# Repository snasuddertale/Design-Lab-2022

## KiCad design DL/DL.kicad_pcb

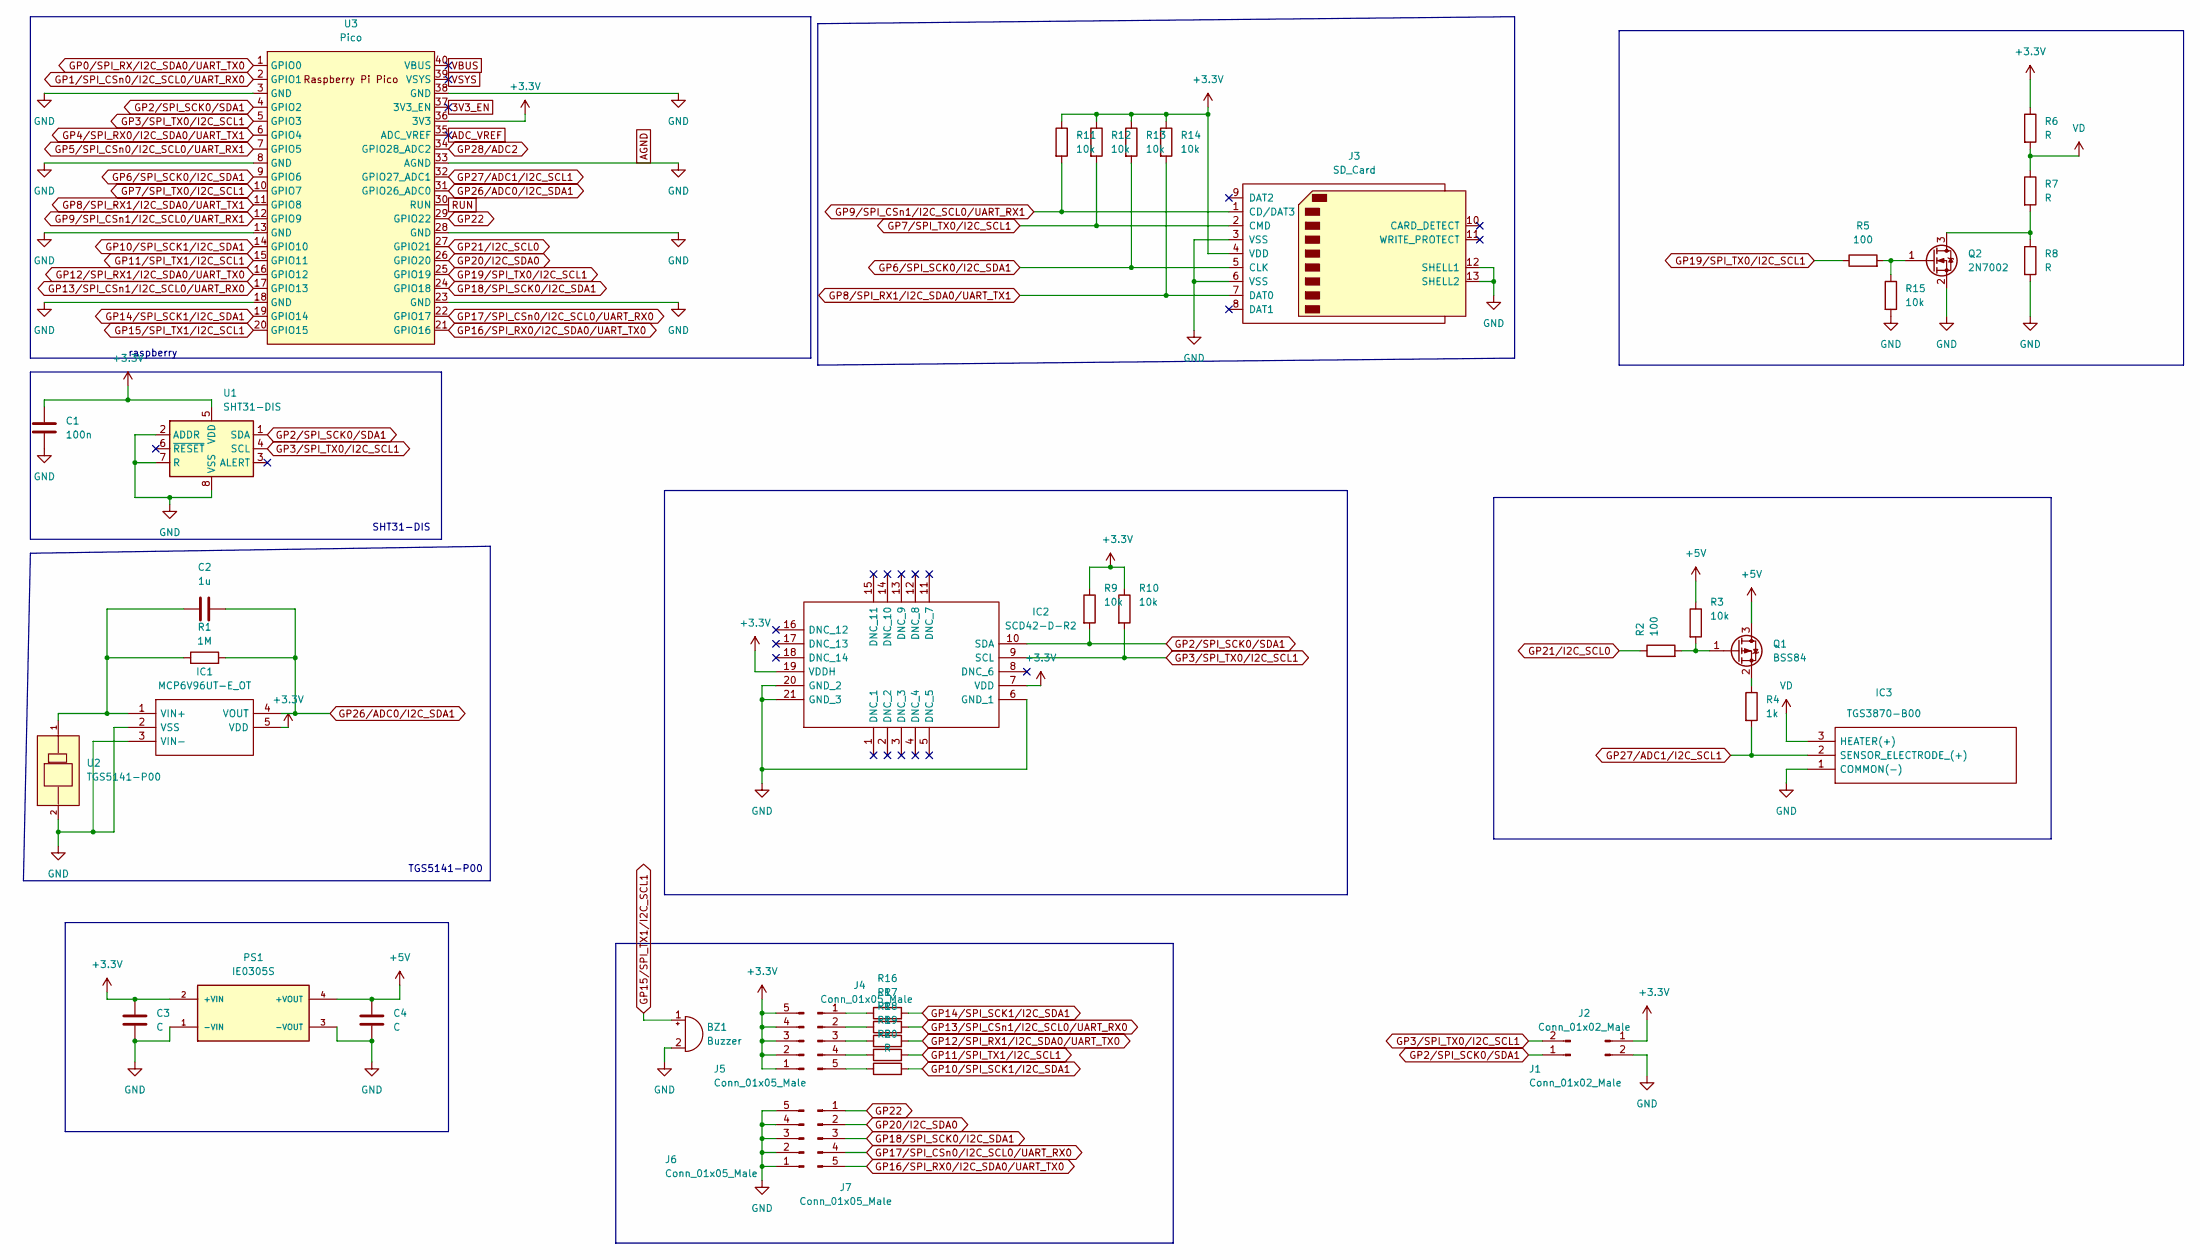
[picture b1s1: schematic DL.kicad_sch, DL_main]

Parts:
BZ1: Buzzer; Buzzer_12x9.5RM7.6
C1: 100n; C_0805_2012Metric_Pad1.18x1.45mm_HandSolder
C2: 1u; C_0805_2012Metric_Pad1.18x1.45mm_HandSolder
C3, C4: C; C_0805_2012Metric_Pad1.18x1.45mm_HandSolder
IC1: MCP6V96UT-E_OT; SOT95P280X145-5N; Mouser Part Number 579-MCP6V96UT-E/OT
IC2: SCD42-D-R2; SCD42DR2; Manufacturer_Part_Number SCD42-D-R2; Mouser Part Number 403-SCD42-D-R2
IC3: TGS3870-B00; TGS3870B00; Manufacturer_Part_Number TGS3870-B00
J1, J2: Conn_01x02_Male; PinHeader_1x02_P2.54mm_Vertical
J3: SD_Card; SD_Kyocera_145638009211859+
J4, J5, J6, J7: Conn_01x05_Male; PinHeader_1x05_P2.54mm_Vertical
PS1: IE0305S; CONV_IE0305S; PARTREV 04-Feb-13
Q1: BSS84; SOT-23
Q2: 2N7002; SOT-23
R1: 1M; R_0805_2012Metric_Pad1.20x1.40mm_HandSolder
R2, R5: 100; R_0805_2012Metric_Pad1.20x1.40mm_HandSolder
R3, R9, R10, R11, R12, R13, R14, R15: 10k; R_0805_2012Metric_Pad1.20x1.40mm_HandSolder
R4: 1k; R_0805_2012Metric_Pad1.20x1.40mm_HandSolder
R6, R7, R8, R16, R17, R18, R19, R20: R; R_0805_2012Metric_Pad1.20x1.40mm_HandSolder
U1: SHT31-DIS; Sensirion_DFN-8-1EP_2.5x2.5mm_P0.5mm_EP1.1x1.7mm
U2: TGS5141-P00; Figaro-TGS5141-P00-MFG
U3: Pico; RPi_Pico_SMD_TH

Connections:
3V3_EN: U3.37 (3V3_EN)
+3.3V: C1.1, C3.1, IC1.5 (VDD), IC2.7 (VDD), IC2.19 (VDDH), J2.1, J3.4 (VDD), J5.1, J5.2, J5.3, J5.4, J5.5, PS1.2 (+VIN), R6.1, R9.1, R10.1, R11.1, R12.1, R13.1, R14.1, U1.5 (VDD), U3.36 (3V3)
+5V: C4.1, PS1.4 (+VOUT), Q1.3 (D), R3.1
ADC_VREF: U3.35 (ADC_VREF)
AGND: BZ1.2 (+), C1.2, C3.2, C4.2, IC1.2 (VSS), IC1.3 (VIN-), IC2.6 (GND_1), IC2.20 (GND_2), IC2.21 (GND_3), IC3.1 (COMMON(-)), J2.2, J3.3 (VSS), J3.6 (VSS), J3.12 (SHELL1), J3.13 (SHELL2), J6.1, J6.2, J6.3, J6.4, J6.5, PS1.1 (-VIN), PS1.3 (-VOUT), Q2.2 (S), R8.2, R15.2, U1.2 (ADDR), U1.7 (R), U1.8 (VSS), U1.9 (VSS), U2.2 (Counter), U3.3 (GND), U3.8 (GND), U3.13 (GND), U3.18 (GND), U3.23 (GND), U3.28 (GND), U3.33 (AGND), U3.38 (GND)
GP0/SPI_RX/I2C_SDA0/UART_TX0: U3.1 (GPIO0)
GP1/SPI_CSn0/I2C_SCL0/UART_RX0: U3.2 (GPIO1)
GP2/SPI_SCK0/SDA1: IC2.10 (SDA), J1.1, R9.2, U1.1 (SDA), U3.4 (GPIO2)
GP3/SPI_TX0/I2C_SCL1: IC2.9 (SCL), J1.2, R10.2, U1.4 (SCL), U3.5 (GPIO3)
GP4/SPI_RX0/I2C_SDA0/UART_TX1: U3.6 (GPIO4)
GP5/SPI_CSn0/I2C_SCL0/UART_RX1: U3.7 (GPIO5)
GP6/SPI_SCK0/I2C_SDA1: J3.5 (CLK), R13.2, U3.9 (GPIO6)
GP7/SPI_TX0/I2C_SCL1: J3.2 (CMD), R12.2, U3.10 (GPIO7)
GP8/SPI_RX1/I2C_SDA0/UART_TX1: J3.7 (DAT0), R14.2, U3.11 (GPIO8)
GP9/SPI_CSn1/I2C_SCL0/UART_RX1: J3.1 (CD/DAT3), R11.2, U3.12 (GPIO9)
GP10/SPI_SCK1/I2C_SDA1: R20.2, U3.14 (GPIO10)
GP11/SPI_TX1/I2C_SCL1: R19.2, U3.15 (GPIO11)
GP12/SPI_RX1/I2C_SDA0/UART_TX0: R18.2, U3.16 (GPIO12)
GP13/SPI_CSn1/I2C_SCL0/UART_RX0: R17.2, U3.17 (GPIO13)
GP14/SPI_SCK1/I2C_SDA1: R16.2, U3.19 (GPIO14)
GP15/SPI_TX1/I2C_SCL1: BZ1.1 (-), U3.20 (GPIO15)
GP16/SPI_RX0/I2C_SDA0/UART_TX0: J7.5, U3.21 (GPIO16)
GP17/SPI_CSn0/I2C_SCL0/UART_RX0: J7.4, U3.22 (GPIO17)
GP18/SPI_SCK0/I2C_SDA1: J7.3, U3.24 (GPIO18)
GP19/SPI_TX0/I2C_SCL1: R5.1, U3.25 (GPIO19)
GP20/I2C_SDA0: J7.2, U3.26 (GPIO20)
GP21/I2C_SCL0: R2.1, U3.27 (GPIO21)
GP22: J7.1, U3.29 (GPIO22)
GP26/ADC0/I2C_SDA1: C2.2, IC1.4 (VOUT), R1.2, U3.31 (GPIO26_ADC0)
GP27/ADC1/I2C_SCL1: IC3.2 (SENSOR_ELECTRODE_(+)), R4.2, U3.32 (GPIO27_ADC1)
GP28/ADC2: U3.34 (GPIO28_ADC2)
unnamed: C2.1, IC1.1 (VIN+), R1.1, U2.1 (Working)
unnamed: J4.1, R16.1
unnamed: J4.2, R17.1
unnamed: J4.3, R18.1
unnamed: J4.4, R19.1
unnamed: J4.5, R20.1
unnamed: Q1.1 (G), R2.2, R3.2
unnamed: Q1.2 (S), R4.1
unnamed: Q2.1 (G), R5.2, R15.1
unnamed: Q2.3 (D), R7.2, R8.1
RUN: U3.30 (RUN)
VBUS: U3.40 (VBUS)
VD: IC3.3 (HEATER(+)), R6.2, R7.1
VSYS: U3.39 (VSYS)

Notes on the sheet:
raspberry
TGS5141-P00
SHT31-DIS

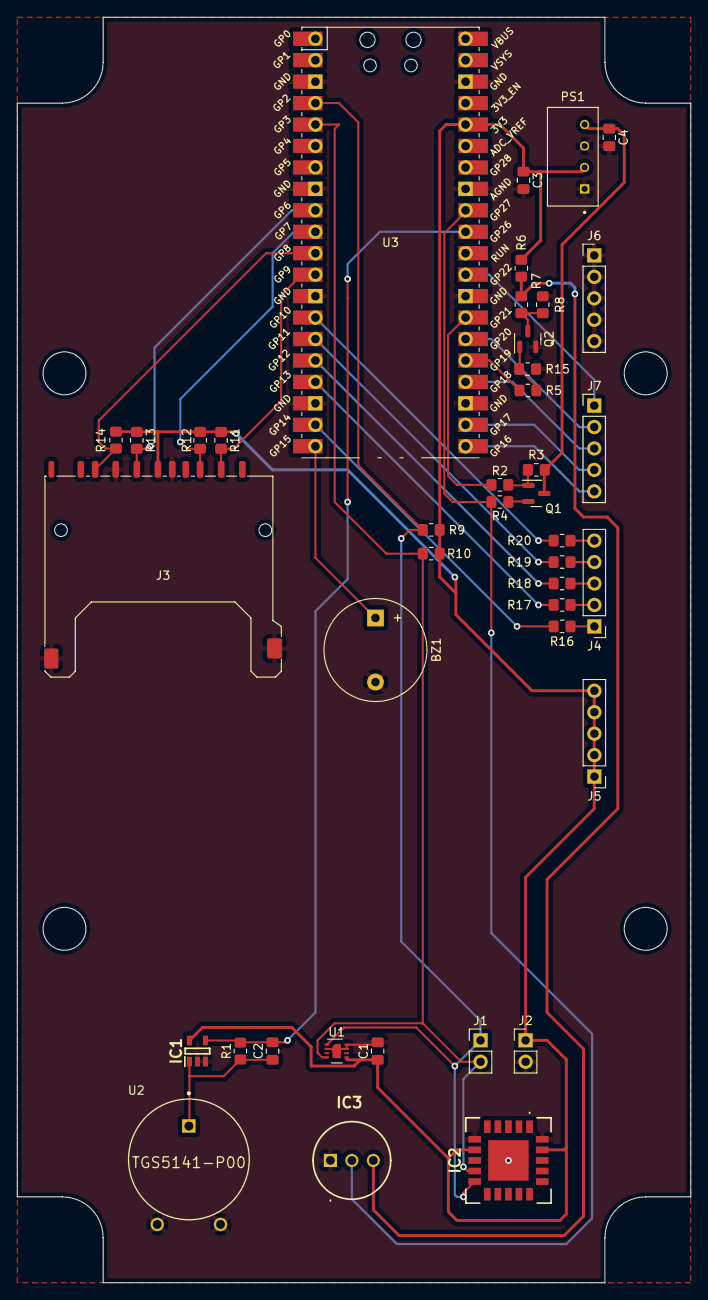
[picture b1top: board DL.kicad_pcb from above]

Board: 2 copper layers, 79.8 x 149.9 mm, 41 parts (0 on the bottom side), 35 nets.

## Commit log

2022-10-16 Add files via upload
    Cały folder z KiCada
2022-10-24 All sensors wiring
2022-10-29 Complete electric scheme
2022-11-06 PCB layout interation no. 1
2022-11-07 PCB layout interation no. 2
2022-11-07 Add files via upload
    Updated pinout 1/2
2022-11-07 Add files via upload
    Updated footprint 2/2 [I'm an idiot]
2022-11-07 Add files via upload
    Yet another push, imma check if it loads properly
2022-11-07 Add files via upload
    Hopefully last update, use .pretty lib for TGS3870
2022-11-08 Fixed edge cuts - Iteration no. 3
2022-11-08 Add files via upload
    Edge cut value fix
2022-11-08 Add files via upload
    Locked Edge Cuts layer with incuts for studs
2022-11-09 Git cynchro fixed
2022-11-09 Add files via upload
    Added mounting holes, all items on edgeCuts layer are locked in place
2022-11-09 Final PCB design
2022-11-10 Add files via upload
    Added carrot logo on back silkscreen, created gerbers
2022-11-10 PCB Final
    The definitive version of PCB design, generated gerber files and sent to the manufacturer
2022-12-18 Firmware prototype
    Prototype design of the software which has been used to test raspberry pi pico on the breadboard
2023-01-30 Final firmware code
    The main.py file, that made our project work and some additional test files, that were used
